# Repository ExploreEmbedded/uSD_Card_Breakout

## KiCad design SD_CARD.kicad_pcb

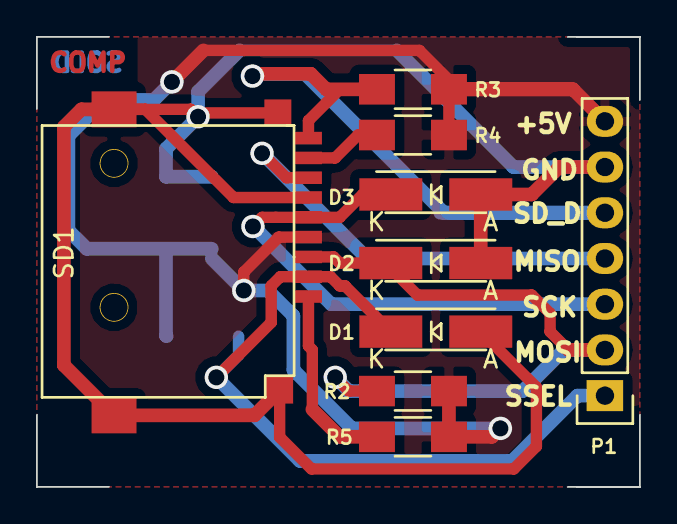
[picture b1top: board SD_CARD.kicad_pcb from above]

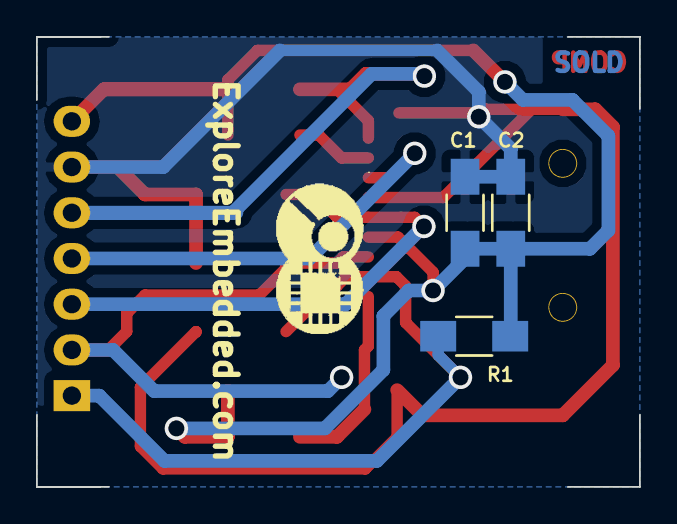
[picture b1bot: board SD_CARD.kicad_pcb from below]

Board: 2 copper layers, 33.5 x 25.0 mm, 13 parts (4 on the bottom side), 9 nets.

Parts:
C1: 100nF; C_1206_HandSoldering
C2: 10uF; C_1206_HandSoldering
D1, D2, D3: ZENER; ZenerDiode_SMD
LOGO: LOGO (2)
P1: CONN_01X07; Pin_Header_Straight_1x07
R1, R2: 10k; R_1206_HandSoldering
R3: 1K; R_1206_HandSoldering
R4, R5: 33K; R_1206_HandSoldering
SD1: MICRO_SD; Micro_SD

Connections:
5V: C1.1, C2.1, P1.7, R1.1, R2.1, R3.1, R4.2, R5.2, SD1.4
/MISO: P1.4, SD1.7
/MOSI: D2.2, P1.2, R2.2, SD1.3
/SCK: D3.2, P1.3, SD1.5
/SD_DETECT: P1.5, R3.2, SD1.9
/SSEL: D1.2, P1.1, R1.2, SD1.2
GND: C1.2, C2.2, D1.1, D2.1, D3.1, P1.6, SD1.6, SD1.10, SD1.11, SD1.12, SD1.13
unnamed: R4.1, SD1.8
unnamed: R5.1, SD1.1

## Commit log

2015-06-29 Added design files
2015-06-30 added corrected files
